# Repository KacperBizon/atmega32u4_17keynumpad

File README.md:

# 17keynumpad

### board pinout
| pin/pin | B5(9) | (B6(14) | B2(16) | B3(10) 
|-------|:-------:|----:|--------:|--------:|
| B4(8) |backspace|  / |    *    |     -   |
|E6(7)  |   7     |  8 |    9    |    N/A  |
| D7(6) |   4     |  5 |    6    |     +   |
| C6(5) |   1     |  2 |    3    |    N/A  |
| D4(4) |  N/A    |  0 |    .    |   Enter |
 
### LCD I2C 16x2 pinout
| Arduino | I2C|
|----------|----------|
| GND   | GND|
| VCC   | VCC|
| 2  | SDA|
| 3  | SCL|

### keypresses
enter:
- first press - shows result
- second press - repeat the operation...
- changes value of "left" to result of the operation

del / num:
- press - deletes last pressed character
- press after the operation changes value of "left" to result of the operation and deletes last character
- hold - changes mode, saves left, middle, right
- hold after the operation changes value of "left" to result of the operation and changes mode

### display
  fp64lib 64 bit float  - IEE754 double with few compromises
  display up max        - 12 + 1 + 1 + 2 (numbers + positive/negative + operation + dots)
  display down          - 12 + 1 + 1 (result (truncated to 12 chars) + positive/negative + dot)

### parts list
- pcb
- 17 1n4148 diodes
- 3x2U pcb stabilizers
- pro micro ATMEGA32U4 (make sure to solder it on the bottom with 'front' orientation)
- 16x2 i2c lcd screen
- toggle switch
- 17 switches
- 17 keycaps
- 4 m2 screws
- 4 m3 screws
- 4 orings
- tp4056 (optional)
- lipo 800/600 mAh battery (optional)

### Acknowledgment
Special thanks to [PCBWay](https://www.pcbway.com) for sponsoring the CNC-machined aluminum case for this project. Their customer service team was quick to answer questions, machining quality and anodization of the enclosure is clean and precise.

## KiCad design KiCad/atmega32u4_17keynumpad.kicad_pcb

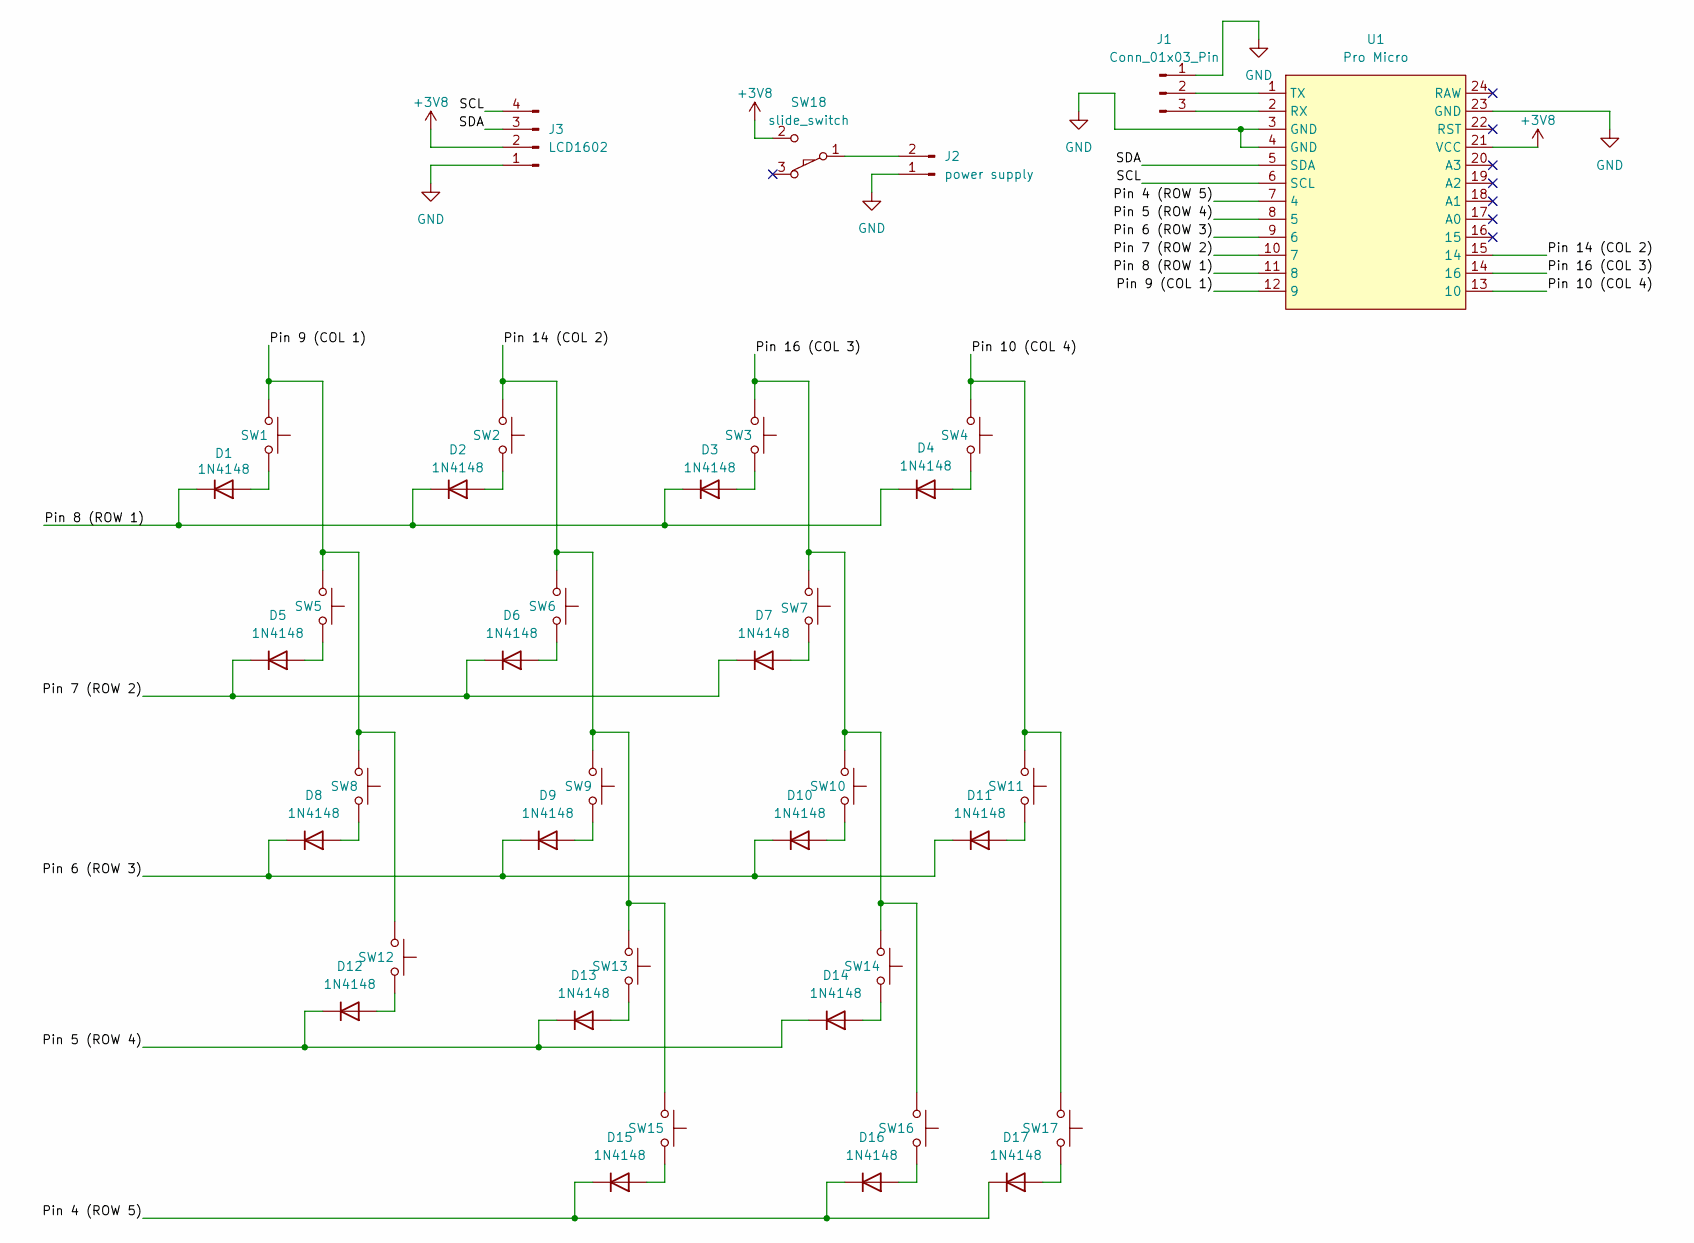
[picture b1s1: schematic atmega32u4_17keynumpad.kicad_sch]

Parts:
D1, D2, D3, D4, D5, D6, D7, D8, D9, D10, D11, D12, D13, D14, D15, D16, D17: 1N4148; D_DO-35_SOD27_P7.62mm_Horizontal
J1: Conn_01x03_Pin; PinHeader_1x03_P2.54mm_Vertical
J2: power supply; PinSocket_1x02_P2.54mm_Vertical
J3: LCD1602; PinHeader_1x04_P2.54mm_Vertical
SW1, SW2, SW3, SW4, SW5, SW6, SW7, SW8, SW9, SW10, SW12, SW13, SW14, SW16: SW_Push; SW_Cherry_MX_PCB_1.00u
SW11, SW15, SW17: SW_Push; SW_Cherry_MX_PCB_2.00u
SW18: slide_switch; SW_Slide-03_Wuerth-WS-SLTV_10x2.5x6.4_P2.54mm
U1: Pro Micro

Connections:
+3V8: J3.2, SW18.2 (B), U1.21 (VCC)
/Pin 4 (ROW 5): D15.1 (K), D16.1 (K), D17.1 (K), U1.7 (4)
/Pin 5 (ROW 4): D12.1 (K), D13.1 (K), D14.1 (K), U1.8 (5)
/Pin 6 (ROW 3): D8.1 (K), D9.1 (K), D10.1 (K), D11.1 (K), U1.9 (6)
/Pin 7 (ROW 2): D5.1 (K), D6.1 (K), D7.1 (K), U1.10 (7)
/Pin 8 (ROW 1): D1.1 (K), D2.1 (K), D3.1 (K), D4.1 (K), U1.11 (8)
/Pin 9 (COL 1): SW1.1, SW5.1, SW8.1, SW12.1, U1.12 (9)
/Pin 10 (COL 4): SW4.1, SW11.1, SW17.1, U1.13 (10)
/Pin 14 (COL 2): SW2.1, SW6.1, SW9.1, SW13.1, SW15.1, U1.15 (14)
/Pin 16 (COL 3): SW3.1, SW7.1, SW10.1, SW14.1, SW16.1, U1.14 (16)
/SCL: J3.4, U1.6 (SCL)
/SDA: J3.3, U1.5 (SDA)
GND: J1.1, J2.1, J3.1, U1.3 (GND), U1.4 (GND), U1.23 (GND)
unnamed: D1.2 (A), SW1.2
unnamed: D2.2 (A), SW2.2
unnamed: D3.2 (A), SW3.2
unnamed: D4.2 (A), SW4.2
unnamed: D5.2 (A), SW5.2
unnamed: D6.2 (A), SW6.2
unnamed: D7.2 (A), SW7.2
unnamed: D8.2 (A), SW8.2
unnamed: D9.2 (A), SW9.2
unnamed: D10.2 (A), SW10.2
unnamed: D11.2 (A), SW11.2
unnamed: D12.2 (A), SW12.2
unnamed: D13.2 (A), SW13.2
unnamed: D14.2 (A), SW14.2
unnamed: D15.2 (A), SW15.2
unnamed: D16.2 (A), SW16.2
unnamed: D17.2 (A), SW17.2
unnamed: J1.2, U1.1 (TX)
unnamed: J1.3, U1.2 (RX)
unnamed: J2.2, SW18.1 (A)

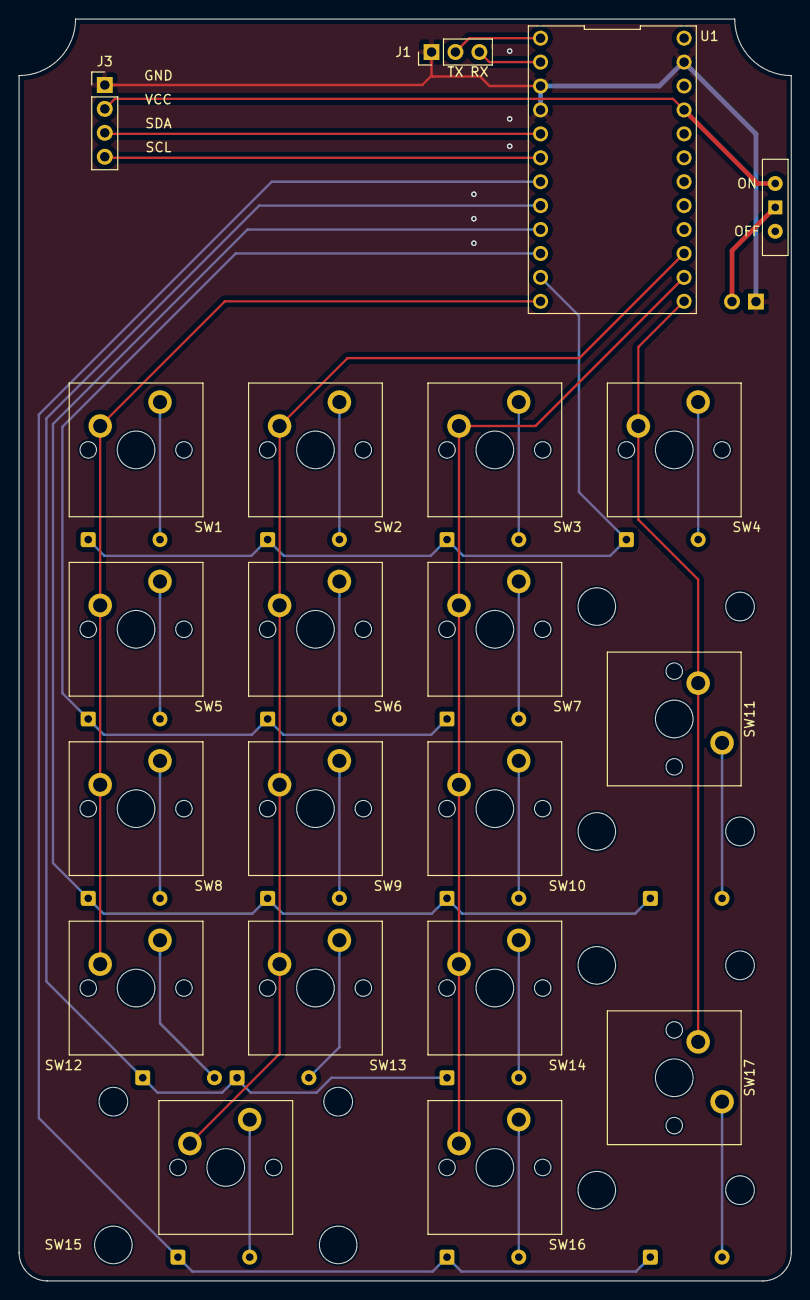
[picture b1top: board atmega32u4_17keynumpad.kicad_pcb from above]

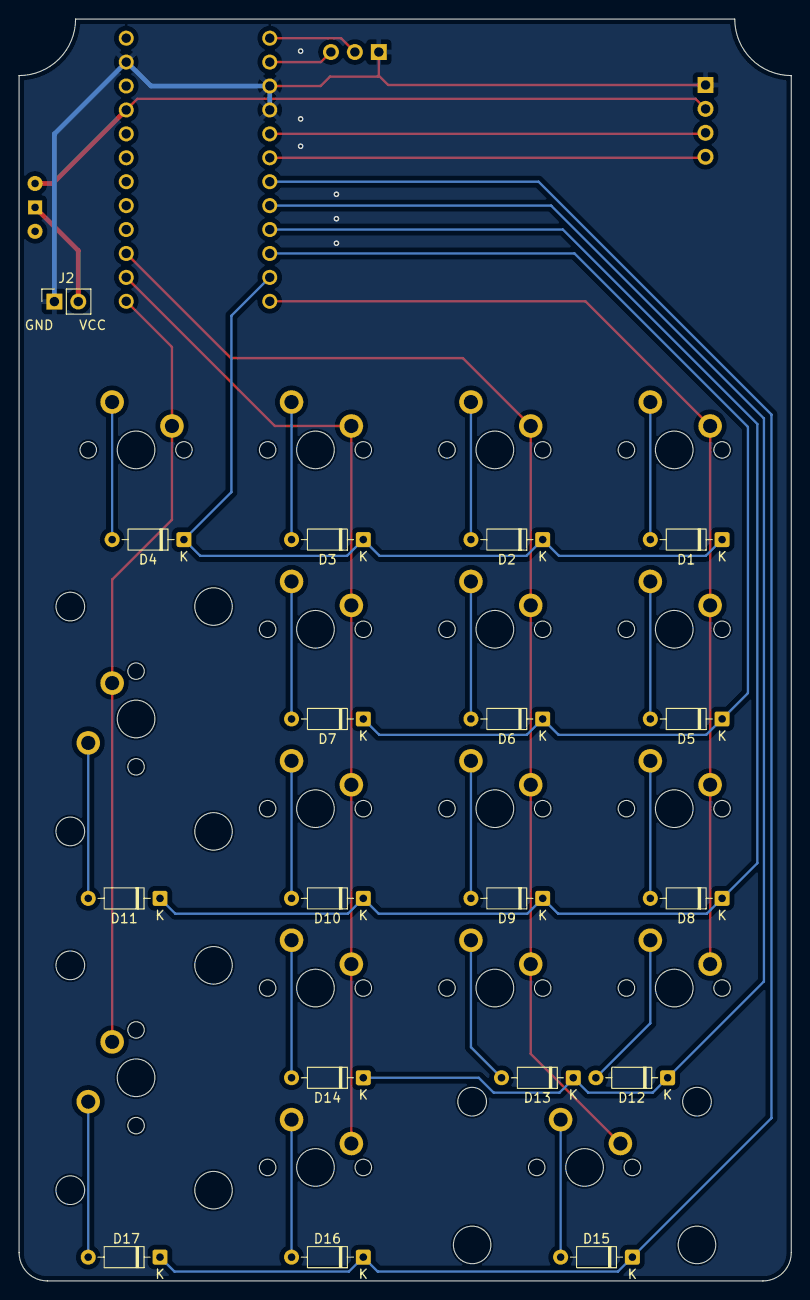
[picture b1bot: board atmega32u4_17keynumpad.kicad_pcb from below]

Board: 2 copper layers, 82.0 x 134.0 mm, 39 parts (18 on the bottom side), 33 nets.

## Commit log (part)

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2025-10-30 added calculator image + case
2025-12-26 add pcb schematic
2025-12-26 pcb fix
2025-12-27 finished pcb
2025-12-27 Update pro micro ATMEGA32U4 soldering instructions
2025-12-27 Add MIT License
2026-06-11 Add PCBWay acknowledgment
2026-06-13 Update case files
